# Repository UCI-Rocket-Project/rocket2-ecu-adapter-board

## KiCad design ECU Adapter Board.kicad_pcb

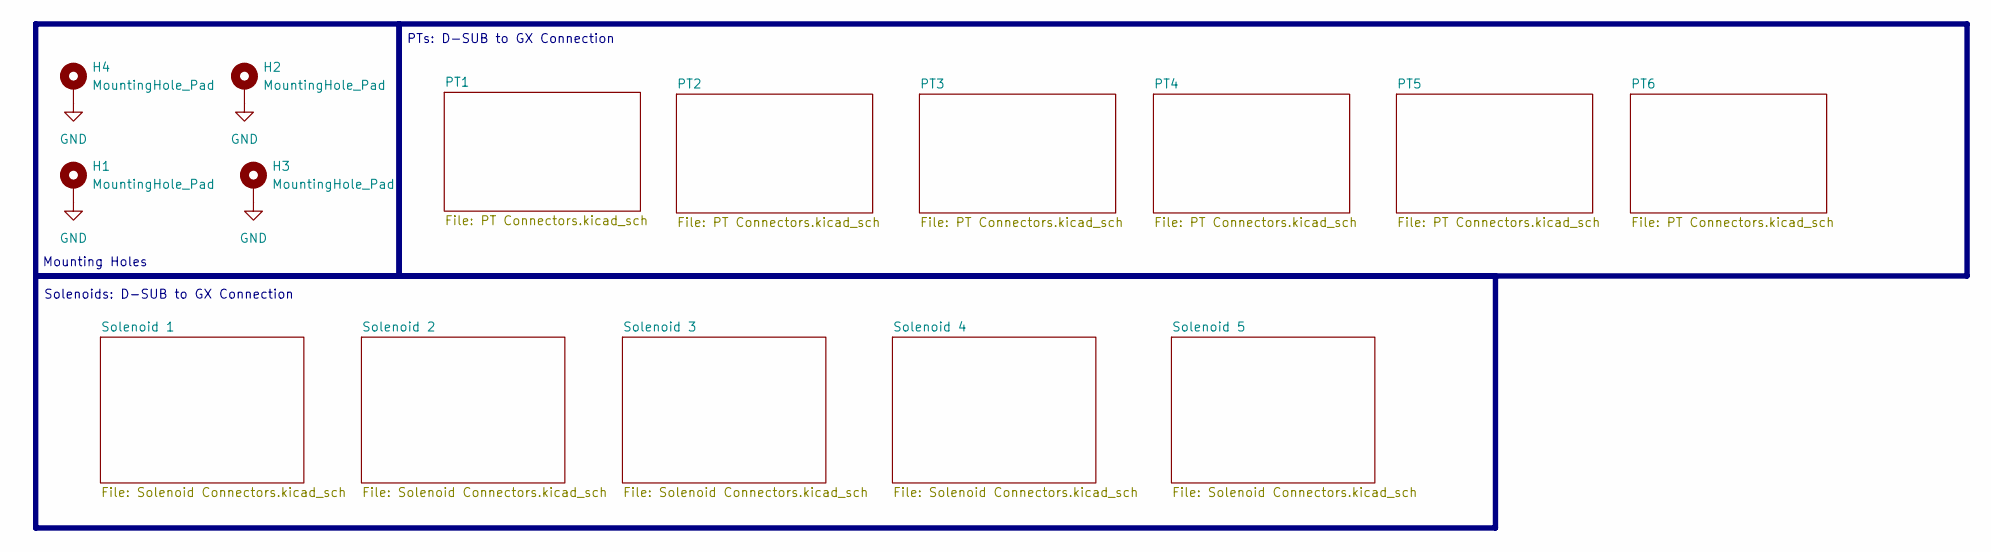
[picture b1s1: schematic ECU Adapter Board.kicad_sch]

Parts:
H1, H2, H3, H4: MountingHole_Pad; MountingHole_4.3mm_M4_Pad_Via

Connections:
GND: H1.1, H2.1, H3.1, H4.1; also elsewhere on the board

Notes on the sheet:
PTs: D-SUB to GX Connection
Solenoids: D-SUB to GX Connection
Mounting Holes

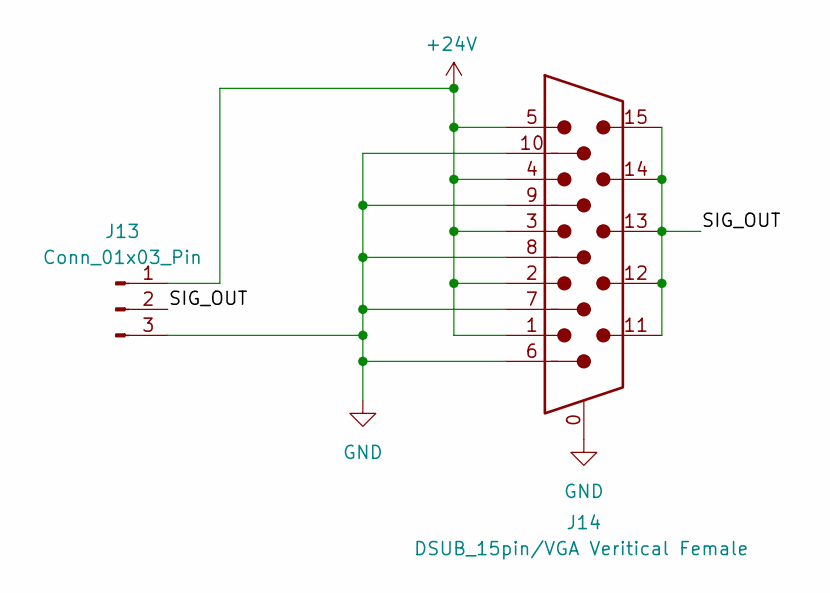
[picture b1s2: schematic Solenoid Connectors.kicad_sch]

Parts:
J13: Conn_01x03_Pin; PinHeader_1x03_P2.54mm_Vertical
J14: DSUB_15pin/VGA Veritical Female; Connector_VGA_Vertical

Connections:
+24V: J13.1, J14.1, J14.2, J14.3, J14.4, J14.5; also elsewhere on the board
/Solenoid 1/SIG_OUT: J13.2, J14.11, J14.12, J14.13, J14.14, J14.15
GND: J13.3, J14.0, J14.6, J14.7, J14.8, J14.9, J14.10; also elsewhere on the board

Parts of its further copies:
J15, J17, J19, J21: Conn_01x03_Pin; PinHeader_1x03_P2.54mm_Vertical
J16, J18, J20, J22: DSUB_15pin/VGA Veritical Female; Connector_VGA_Vertical

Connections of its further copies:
+24V: J15.1, J16.1, J16.2, J16.3, J16.4, J16.5, J17.1, J18.1, J18.2, J18.3, J18.4, J18.5, J19.1, J20.1, J20.2, J20.3, J20.4, J20.5, J21.1, J22.1, J22.2, J22.3, J22.4, J22.5; also elsewhere on the board
/Solenoid 2/SIG_OUT: J15.2, J16.11, J16.12, J16.13, J16.14, J16.15
/Solenoid 3/SIG_OUT: J17.2, J18.11, J18.12, J18.13, J18.14, J18.15
/Solenoid 4/SIG_OUT: J19.2, J20.11, J20.12, J20.13, J20.14, J20.15
/Solenoid 5/SIG_OUT: J21.2, J22.11, J22.12, J22.13, J22.14, J22.15
GND: J15.3, J16.0, J16.6, J16.7, J16.8, J16.9, J16.10, J17.3, J18.0, J18.6, J18.7, J18.8, J18.9, J18.10, J19.3, J20.0, J20.6, J20.7, J20.8, J20.9, J20.10, J21.3, J22.0, J22.6, J22.7, J22.8, J22.9, J22.10; also elsewhere on the board

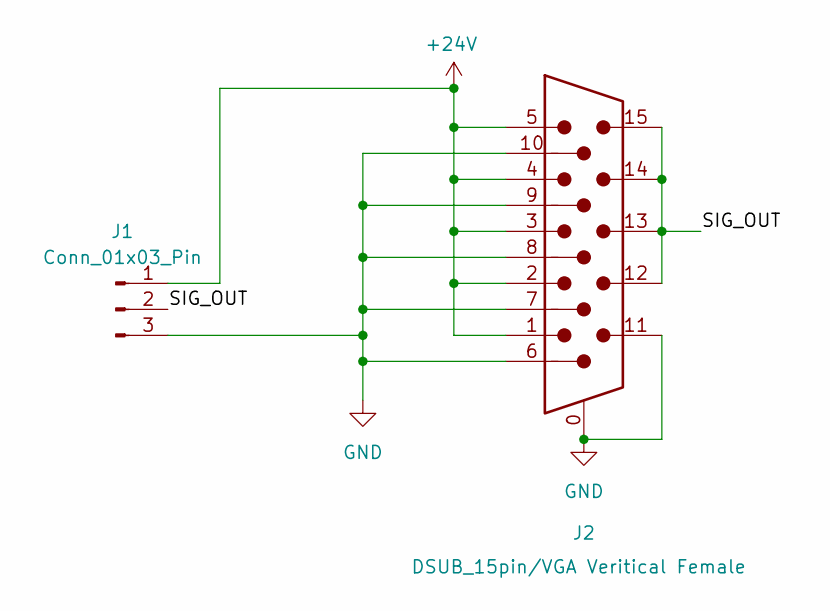
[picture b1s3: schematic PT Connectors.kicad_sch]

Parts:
J1: Conn_01x03_Pin; PinHeader_1x03_P2.54mm_Vertical
J2: DSUB_15pin/VGA Veritical Female; Connector_VGA_Vertical

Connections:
+24V: J1.1, J2.1, J2.2, J2.3, J2.4, J2.5; also elsewhere on the board
/PT1/SIG_OUT: J1.2, J2.12, J2.13, J2.14, J2.15
GND: J1.3, J2.0, J2.6, J2.7, J2.8, J2.9, J2.10, J2.11; also elsewhere on the board

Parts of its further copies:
J3, J5, J7, J9, J11: Conn_01x03_Pin; PinHeader_1x03_P2.54mm_Vertical
J4, J6, J8, J10, J12: DSUB_15pin/VGA Veritical Female; Connector_VGA_Vertical

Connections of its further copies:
+24V: J3.1, J4.1, J4.2, J4.3, J4.4, J4.5, J5.1, J6.1, J6.2, J6.3, J6.4, J6.5, J7.1, J8.1, J8.2, J8.3, J8.4, J8.5, J9.1, J10.1, J10.2, J10.3, J10.4, J10.5, J11.1, J12.1, J12.2, J12.3, J12.4, J12.5; also elsewhere on the board
/PT2/SIG_OUT: J3.2, J4.12, J4.13, J4.14, J4.15
/PT3/SIG_OUT: J5.2, J6.12, J6.13, J6.14, J6.15
/PT4/SIG_OUT: J7.2, J8.12, J8.13, J8.14, J8.15
/PT5/SIG_OUT: J9.2, J10.12, J10.13, J10.14, J10.15
/PT6/SIG_OUT: J11.2, J12.12, J12.13, J12.14, J12.15
GND: J3.3, J4.0, J4.6, J4.7, J4.8, J4.9, J4.10, J4.11, J5.3, J6.0, J6.6, J6.7, J6.8, J6.9, J6.10, J6.11, J7.3, J8.0, J8.6, J8.7, J8.8, J8.9, J8.10, J8.11, J9.3, J10.0, J10.6, J10.7, J10.8, J10.9, J10.10, J10.11, J11.3, J12.0, J12.6, J12.7, J12.8, J12.9, J12.10, J12.11; also elsewhere on the board

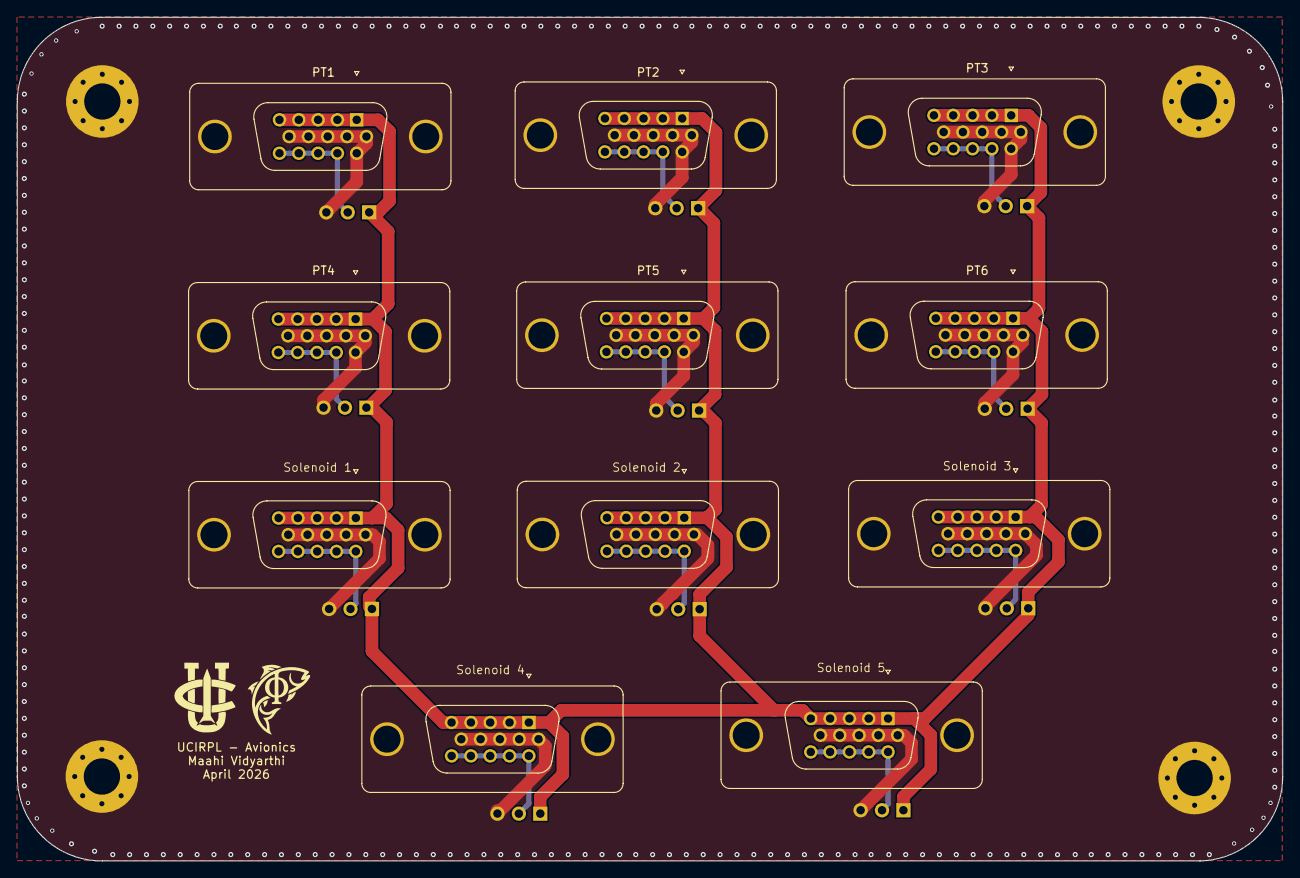
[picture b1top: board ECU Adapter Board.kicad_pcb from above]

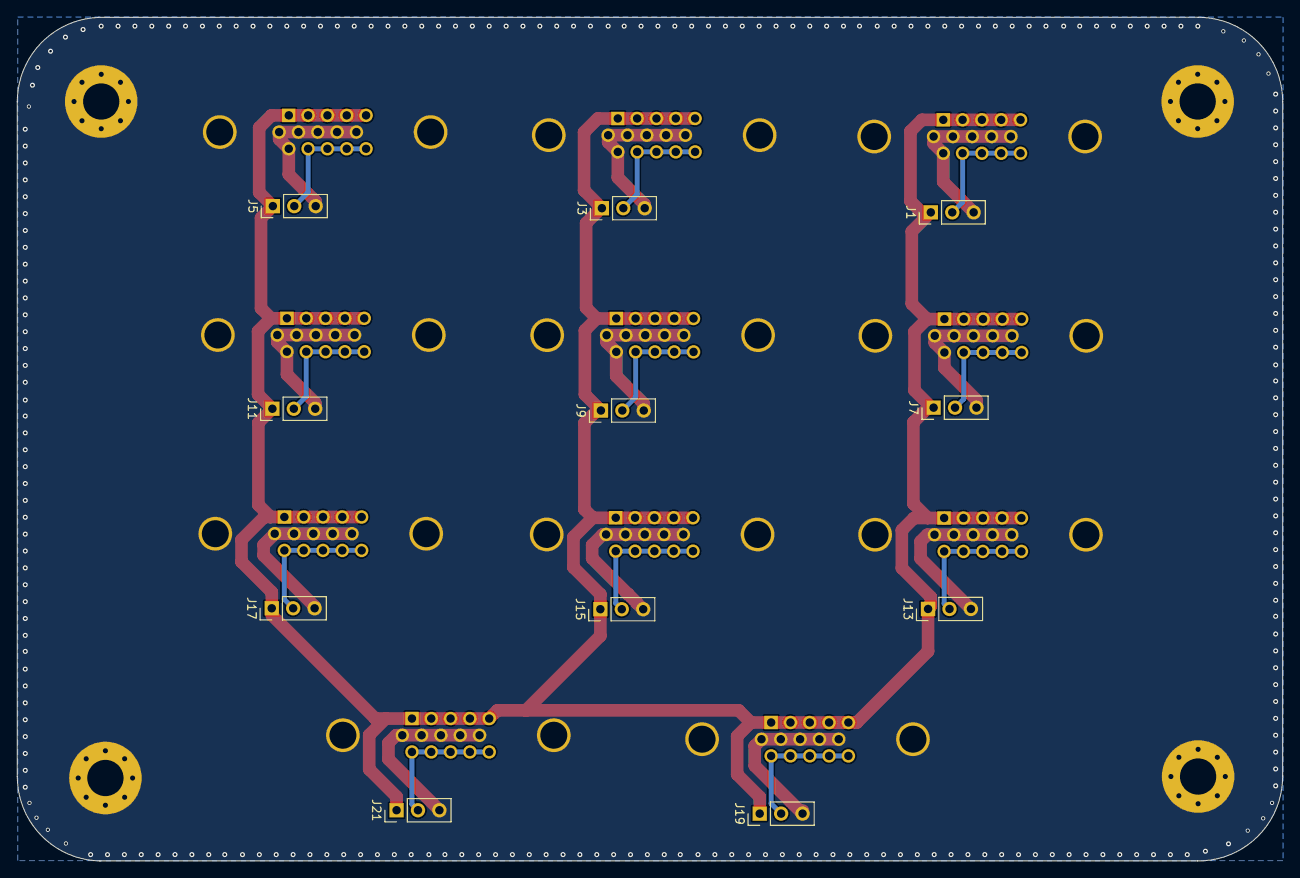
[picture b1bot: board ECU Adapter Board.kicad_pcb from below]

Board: 2 copper layers, 150.0 x 100.0 mm, 26 parts (11 on the bottom side), 13 nets.

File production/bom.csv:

Designator,Footprint,Quantity,Value,LCSC Part #
"J1, J11, J13, J15, J17, J19, J21, J3, J5, J7, J9",PinHeader_1x03_P2.54mm_Vertical,11,Conn_01x03_Pin,
"J10, J12, J14, J16, J18, J2, J20, J22, J4, J6, J8",Connector_VGA_Vertical,11,DSUB_15pin/VGA Veritical  Female,

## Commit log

2026-03-28 removed unnecessary gnd trace
2026-03-28 grounded mounting holes
2026-03-31 silkscreen labeling, fixed trace thicknesses
2026-04-05 grounded pin 11 on PT Connectors
2026-04-07 added UCIRP repo submodule, fixed silkscreen
2026-04-08 Ready for order
